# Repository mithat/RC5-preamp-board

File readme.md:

RC5-preamp-board
================
_Because remote controlled audio is free and for the people.™_

Hardware design for a remote control receiver based on [RC5-preamp](https://github.com/mithat/RC5-preamp).

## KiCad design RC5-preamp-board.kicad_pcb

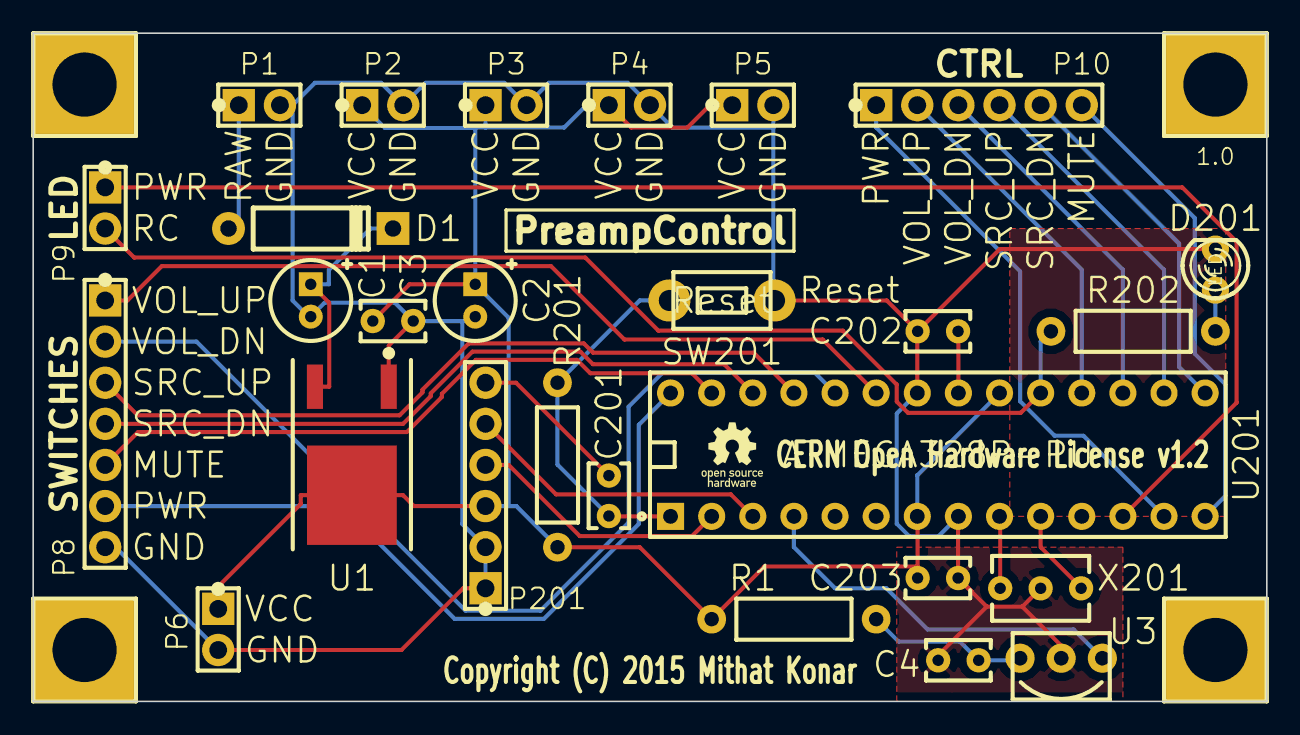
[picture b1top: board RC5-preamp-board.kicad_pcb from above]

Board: 2 copper layers, 76.2 x 41.3 mm, 32 parts (0 on the bottom side), 28 nets.

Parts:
C1, C2: 47u; mfk-CRP_5.0_2.0_0.5
C3, C4, C201, C202, C203: 100n; mfk-C_4.0_2.5_2.5_0.5
D1: 1N4007; mfk-DO-41
D201: LED; LED-3MM
P1: RAW_DC; mfk-SIL-2
P2, P3, P4, P5, P6: VCC; mfk-SIL-2
P8: INPUTS; mfk-SIL-7
P9: UI_OUT; mfk-SIL-2
P10: CTL_OUT; mfk-SIL-6
P201: FTDI Basic; mfk-SIL-6
R1: 330R; mfk-R_0.25W_RN55
R201: 10K; mfk-R_0.25W_RN55
R202: 330; mfk-R_0.25W_RN55
SW201: Reset; mfk-SW_PUSH_6x3.5mm
U1: NCP1117DT50RKG; mfk-IPC7351-trans-TO228P1003X238-3N
U3: TSOP34136; mfk-Vishay-TSOP341xx-alt
U201: ATMEGA328P-PU; mfk-DIP-28_300_rnd
VAL: REF; oshw-logo-150mil-FSilk
X201: CSTLS16M0X53-B0; mfk-Murata-CSTLS_X
mtg1, mtg2, mtg3, mtg4: 621; mfk-KEYSTONE-621

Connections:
/RAW_DC: D1.1, P1.1
/arduino-pcb/A0: P8.1, U201.23
/arduino-pcb/A1: P8.2, U201.24
/arduino-pcb/A2: P8.3, U201.25
/arduino-pcb/A3: P8.4, U201.26
/arduino-pcb/A4: P8.5, U201.27
/arduino-pcb/A5: P8.6, U201.28
/arduino-pcb/AREF: C202.1, U201.21
/arduino-pcb/D2: U3.3, U201.4
/arduino-pcb/D6: P9.1, U201.12
/arduino-pcb/D7: P10.1, U201.13
/arduino-pcb/D8: P10.6, U201.14
/arduino-pcb/D9: P10.5, U201.15
/arduino-pcb/D10: P10.4, U201.16
/arduino-pcb/DTR: C201.1, P201.6
/arduino-pcb/MISO: P10.2, U201.18
/arduino-pcb/MOSI: P10.3, U201.17
/arduino-pcb/RESET: C201.2, R201.2, SW201.1, U201.1
/arduino-pcb/RXI: P201.4, U201.2
/arduino-pcb/SCK: P9.2, R202.1, U201.19
/arduino-pcb/TX0: P201.5, U201.3
/arduino-pcb/V_VCC: C2.1, C3.1, C203.1, P2.1, P3.1, P4.1, P5.1, P6.1, P201.3, R1.1, R201.1, U1.2, U201.7, U201.20
DGND: C1.2, C2.2, C3.2, C4.2, C202.2, C203.2, D201.2, P1.2, P2.2, P3.2, P4.2, P5.2, P6.2, P8.7, P201.1, P201.2, SW201.2, U1.1, U3.2, U201.8, U201.22, X201.3
unnamed: C4.1, R1.2, U3.1
unnamed: C1.1, D1.2, U1.3
unnamed: U201.10, X201.1
unnamed: U201.9, X201.2
unnamed: D201.1, R202.2

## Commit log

2015-04-05 Initial commit.
2015-04-07 Schematic without power supply.
2015-04-07 Schematic capture complete.
2015-04-07 Added IR receiver module to schematic. So it wasn't done after all. :-/
2015-04-07 Schematic presentation refinements and corrected C4.
2015-04-17 Changed from Pro Mini to discrete PCB implementation.
2015-04-18 PCB placed, routability confirmed.
2015-04-19 Dimensioned and routed.
2015-04-19 Shrunk and routed.
2015-04-20 Removed one VCC tap. Keystone 621 mtg added. Routed.
2015-04-20 Silk tweaks.
2015-04-20 Nudged TSOP receiver back so the main body is just a hair recessed from PCB edge.
2015-04-20 Moved module to right side of board.
2015-04-20 Rerouted IR module output away from resonator.
2015-04-24 Created schematic PDF for documentation. Bumped version #.
2015-04-24 Added additional current limitation comments to schematic and increased max. sink per Arduino spec.
2015-04-24 Removed pdfs from documentation ... it doesn't seem like a good idea.

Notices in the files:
RC5-preamp-board.kicad_pcb:
CERN Open Hardware License v1.2
Copyright (C) 2015 Mithat Konar
